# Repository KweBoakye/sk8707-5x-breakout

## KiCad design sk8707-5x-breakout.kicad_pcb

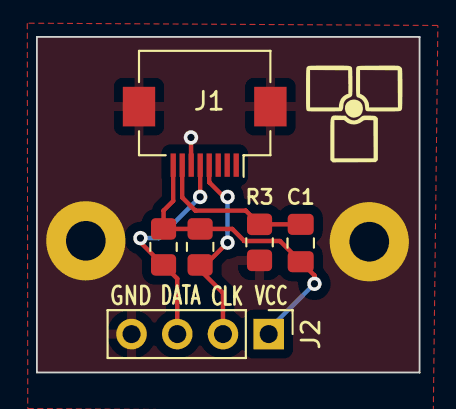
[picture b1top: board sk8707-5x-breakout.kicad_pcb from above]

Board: 2 copper layers, 21.3 x 18.6 mm, 8 parts (0 on the bottom side), 5 nets.

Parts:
C1: 2.2uF; C_0805_2012Metric_Pad1.18x1.45mm_HandSolder
H1, H2: MountingHole; MountingHole_2.2mm_M2_Pad
J1: Conn_01x08_Socket; Hirose_FH12-8S-0.5SH_1x08-1MP_P0.50mm_Horizontal
J2: Conn_01x04_Pin; PinHeader_1x04_P2.54mm_Vertical
R1, R2: 4k7; R_0805_2012Metric_Pad1.20x1.40mm_HandSolder
R3: 100k; R_0805_2012Metric_Pad1.20x1.40mm_HandSolder

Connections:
CLK: J1.4, J2.2, R2.2
DATA: J1.5, J2.3, R1.2
GND: H1.1, H2.1, J1.6, J1.MP, J2.4, R3.2
IPD RST: C1.2, J1.7, R3.1
VCC: C1.1, J1.8, J2.1, R1.1, R2.1

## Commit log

2023-08-12 Initial commit of pcb
2023-08-13 update pcb
2023-08-23 edited routing and grounded mounting holes
2023-08-28 reversed pin order and grounded ffc connector
2023-08-29 added trackpoint silkscreen icon, source image https://www.reddit.com/r/thinkpad/comments/8arjci/wanted_to_share_a_minimalist_trackpoint_wallpaper/
2023-08-30 corrected pin silkscreen labels
